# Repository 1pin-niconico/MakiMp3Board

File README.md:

# MakiMp3Board

逐次ファイル等アップロードしていきます。

KiCADは7.0です。

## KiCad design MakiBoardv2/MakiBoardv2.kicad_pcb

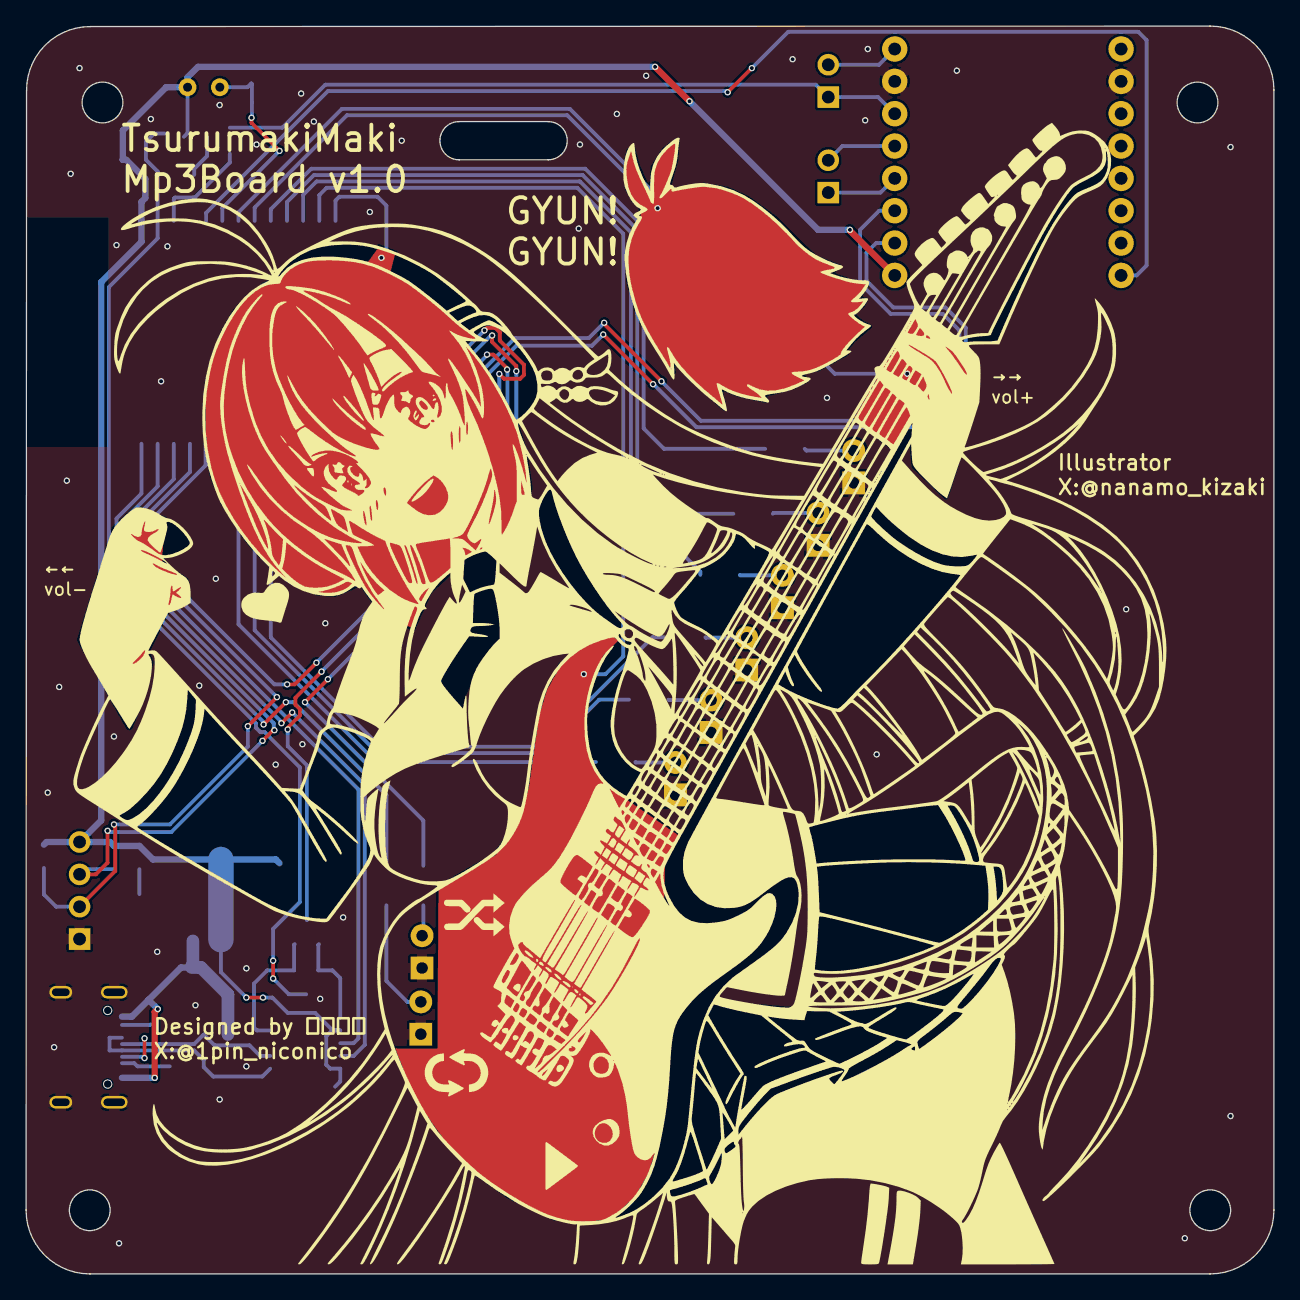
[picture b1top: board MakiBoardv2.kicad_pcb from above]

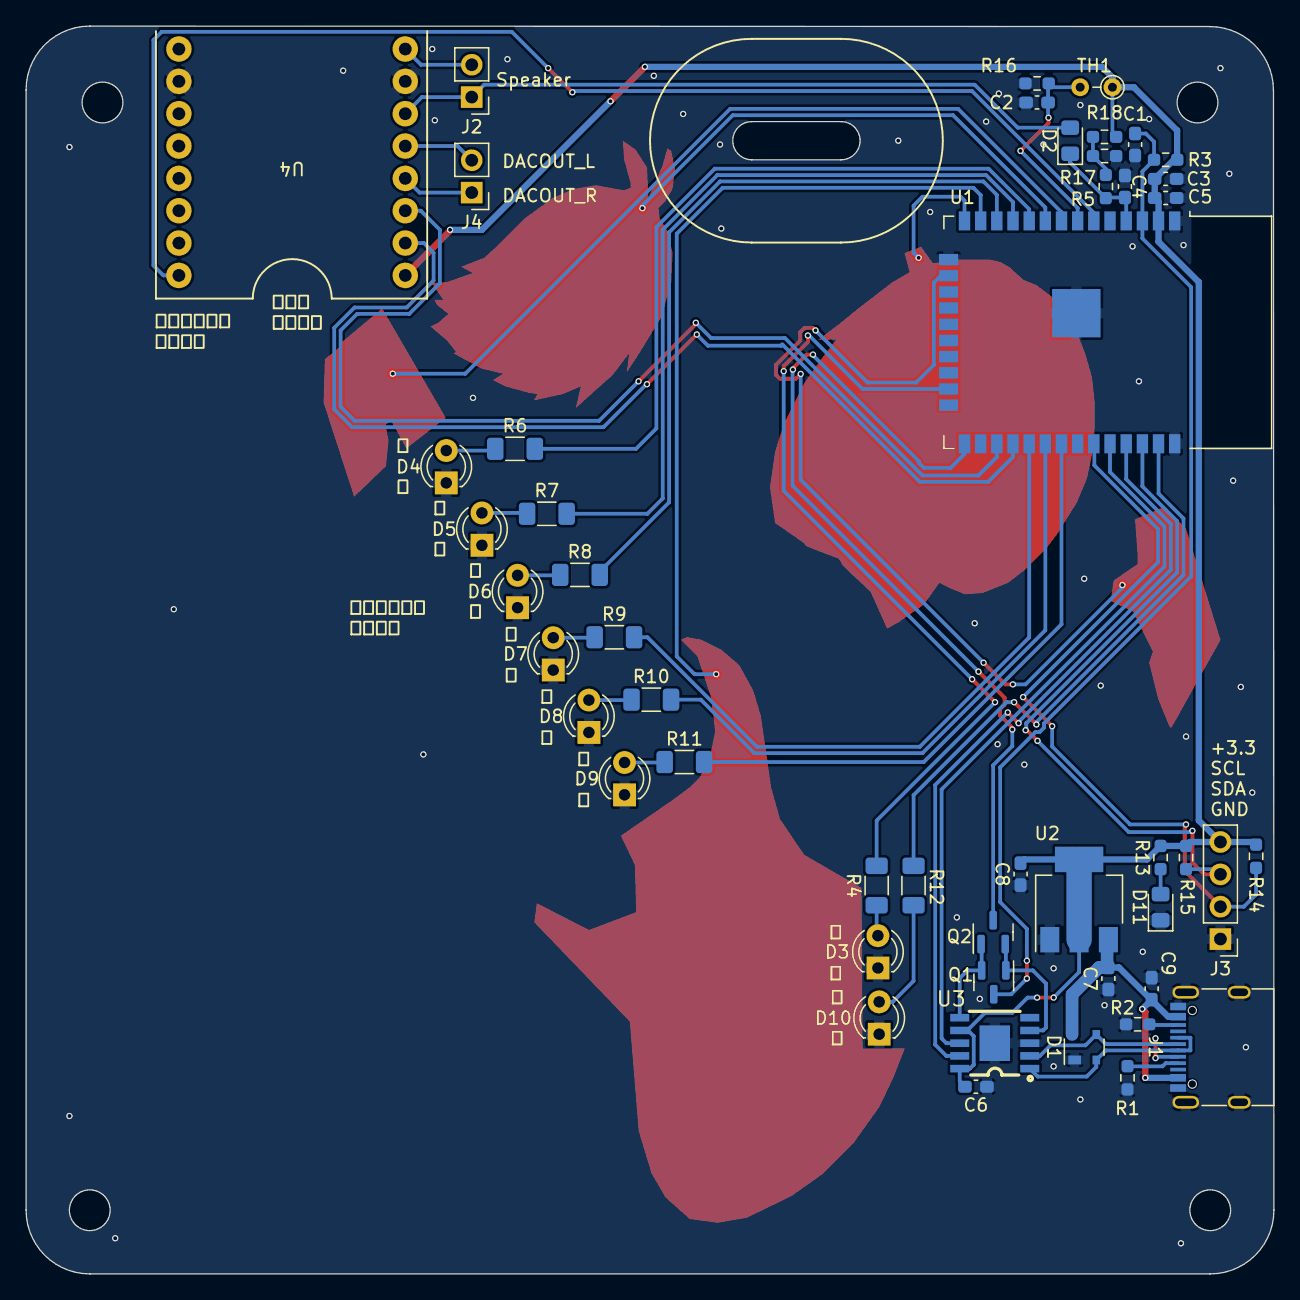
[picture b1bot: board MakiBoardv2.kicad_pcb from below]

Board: 2 copper layers, 98.0 x 98.0 mm, 49 parts (49 on the bottom side), 42 nets.

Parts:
C1, C2, C4, C6: 0.1u; C_0603_1608Metric_Pad1.08x0.95mm_HandSolder
C3, C7, C8, C9: 22u; C_0603_1608Metric_Pad1.08x0.95mm_HandSolder
C5: 1u; C_0603_1608Metric_Pad1.08x0.95mm_HandSolder
D1: PRTR5V0U2X; SOT-143
D2: D_Schottky; D_0805_2012Metric_Pad1.15x1.40mm_HandSolder
D3, D4, D5, D6, D7, D8, D9, D10: LED; LED_D3.0mm
D11: LED; LED_0805_2012Metric_Pad1.15x1.40mm_HandSolder
J1: USB_C_Receptacle_USB2.0; USB_C_Receptacle_G-Switch_GT-USB-7010ASV
J2: speaker; PinHeader_1x02_P2.54mm_Vertical
J3: Conn_01x04_Socket; PinHeader_1x04_P2.54mm_Vertical
J4: Out_speaker; PinHeader_1x02_P2.54mm_Vertical
Q1, Q2: Q_NMOS_GSD; SOT-23
R1, R2: 4.99k; R_0603_1608Metric_Pad0.98x0.95mm_HandSolder
R3, R5, R14, R15, R16: 10k; R_0603_1608Metric_Pad0.98x0.95mm_HandSolder
R4, R6, R7, R8, R9, R10, R11, R12: 220; R_1206_3216Metric_Pad1.30x1.75mm_HandSolder
R13: 220; R_0603_1608Metric_Pad0.98x0.95mm_HandSolder
R17, R18: 1k; R_0603_1608Metric_Pad0.98x0.95mm_HandSolder
TH1: Thermistor; R_Axial_DIN0204_L3.6mm_D1.6mm_P2.54mm_Vertical
U1: ESP32-WROOM-32E; ESP32-WROOM-32D
U2: AZ1117-3.3; SOT-223
U3: CH340K
U4: MP3-TF-16P

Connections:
/3.3V: C3.1, C4.2, C6.2, C8.2, J3.4, R3.2, R13.2, R14.2, R15.2, R18.2, TH1.1, U1.2 (VDD), U2.2 (VO), U2.4 (VO), U3.7 (VCC), U3.10 (V3), U4.1 (VCC)
/BUSY: U1.6 (IO34), U4.16 (BUSY)
/D+: D1.2 (I/O1), J1.A6 (D+), J1.B6 (D+), U3.1 (UD+)
/D-: D1.3 (I/O2), J1.A7 (D-), J1.B7 (D-), U3.2 (UD-)
/EN: C1.1, Q1.3 (D), R3.1, U1.3 (EN)
/ESP_RX0: U1.34 (RXD0/IO3), U3.8 (TXD)
/ESP_RX2: U1.27 (IO16), U4.3 (TX)
/ESP_TX0: U1.35 (TXD0/IO1), U3.9 (RXD)
/ESP_TX2: U1.28 (IO17), U4.2 (RX)
/IO0: Q2.3 (D), U1.25 (IO0)
/LED1: R6.2, U1.10 (IO25)
/LED2: R7.2, U1.11 (IO26)
/LED3: R8.2, U1.12 (IO27)
/LED4: R9.2, U1.29 (IO5)
/LED5: R10.2, U1.30 (IO18)
/LED6: R11.2, U1.31 (IO19)
/LED_MODE: R12.2, U1.37 (IO23)
/LED_SHUFF: R4.2, U1.23 (IO15)
/SCL: J3.3, R15.1, U1.36 (IO22)
/SDA: J3.2, R14.1, U1.33 (IO21)
/SPK1: D2.2 (A), J2.1, U4.6 (SPK_1)
/SPK2: J2.2, U4.8 (SPK_2)
/VT: C2.2, R16.2, TH1.2, U1.7 (IO35)
GND: C1.2, C2.1, C3.2, C4.1, C5.1, C6.1, C7.1, C8.1, C9.2, D1.1 (GND), D3.1 (K), D4.1 (K), D5.1 (K), D6.1 (K), D7.1 (K), D8.1 (K), D9.1 (K), D10.1 (K), D11.1 (K), J1.A1 (GND), J1.A12 (GND), J1.B1 (GND), J1.B12 (GND), J1.S1 (SHIELD), J3.1, R1.1, R2.1, R16.1, R17.2, U1.1 (GND), U1.15 (GND), U1.38 (GND), U1.39 (GND), U2.1 (GND), U3.3 (GND), U3.11 (TP), U4.7 (GND), U4.10 (GND)
unnamed: C7.2, C9.1, D1.4 (VCC), J1.A4 (VBUS), J1.A9 (VBUS), J1.B4 (VBUS), J1.B9 (VBUS), U2.3 (VI)
unnamed: C5.2, D2.1 (K), R5.2, U1.4 (SENSOR_VP)
unnamed: D3.2 (A), R4.1
unnamed: D4.2 (A), R6.1
unnamed: D5.2 (A), R7.1
unnamed: D6.2 (A), R8.1
unnamed: D7.2 (A), R9.1
unnamed: D8.2 (A), R10.1
unnamed: D9.2 (A), R11.1
unnamed: D10.2 (A), R12.1
unnamed: D11.2 (A), R13.1
unnamed: J1.A5 (CC1), R1.2
unnamed: J1.B5 (CC2), R2.2
unnamed: J4.1, U4.4 (DAC_R)
unnamed: J4.2, U4.5 (DAC_L)
unnamed: Q1.1 (G), Q2.2 (S), U3.4 (~DTR)
unnamed: Q1.2 (S), Q2.1 (G), U3.6 (~RTS)
unnamed: R5.1, R17.1, R18.1

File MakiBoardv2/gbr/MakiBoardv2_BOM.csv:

Comment,Designator,Footprint,JLCPCB Part #
0.1u,"C1, C2, C4, C6",Capacitor_SMD:C_0603_1608Metric_Pad1.08x0.95mm_HandSolder,C14663
22u,"C3, C7, C8, C9",Capacitor_SMD:C_0603_1608Metric_Pad1.08x0.95mm_HandSolder,C59461
1u,C5,Capacitor_SMD:C_0603_1608Metric_Pad1.08x0.95mm_HandSolder,C15849
PRTR5V0U2X,D1,Package_TO_SOT_SMD:SOT-143,C3018477
D_Schottky,D2,Diode_SMD:D_0805_2012Metric_Pad1.15x1.40mm_HandSolder,C305421
LED,D11,LED_SMD:LED_0805_2012Metric_Pad1.15x1.40mm_HandSolder,C2297
USB_C_Receptacle_USB2.0,J1,Connector_USB:USB_C_Receptacle_G-Switch_GT-USB-7010ASV,C2988369
Q_NMOS_GSD,"Q1, Q2",Package_TO_SOT_SMD:SOT-23,C8545
4.99k,"R1, R2",Resistor_SMD:R_0603_1608Metric_Pad0.98x0.95mm_HandSolder,C23046
10k,"R3, R5, R14, R15, R16",Resistor_SMD:R_0603_1608Metric_Pad0.98x0.95mm_HandSolder,C25804
220,R13,Resistor_SMD:R_0603_1608Metric_Pad0.98x0.95mm_HandSolder,C22962
1k,"R17, R18",Resistor_SMD:R_0603_1608Metric_Pad0.98x0.95mm_HandSolder,C21190
ESP32-WROOM-32E,U1,RF_Module:ESP32-WROOM-32D,C701341
AZ1117-3.3,U2,Package_TO_SOT_SMD:SOT-223,C108494
CH340K,U3,Makiboard:CH340K,C968586

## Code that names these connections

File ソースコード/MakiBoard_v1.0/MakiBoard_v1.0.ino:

#include "Arduino.h"
#include "EEPROM.h"
#include "BluetoothSerial.h"
#include "WiFi.h"
#include "DFMiniMp3.h"

class Mp3Notify; 
typedef DFMiniMp3<HardwareSerial, Mp3Notify> DfMp3; 
DfMp3 dfmp3(Serial2);

#define LED6 19
#define LED5 18
#define LED4 5
#define LED3 27
#define LED2 26
#define LED1 25
#define LED_LOOP 23
#define LED_SHUFF 15

int playMode=0; //0:mp3再生モード,1:めざましモード
bool tempPause =false; //ポーズ中か否か
bool autoPlay = false; //自動再生モードか否か
bool playFinish = false; //再生が完了しているか否か
bool shuffle = false; //シャッフルモードか否か
bool alert = false;//目覚まし中かどうか
uint32_t timerEN=0;//タイマーモードの可否、上位8bitに目覚ましを鳴らす時刻、下位24bitに時報のEnableが格納
uint8_t previousTrack=0;//最後に再生したトラック
uint8_t f1Number;//フォルダ1内のトラック数
uint8_t f3Number;
uint8_t randomArray[256];

String SSID;//WiFi接続時のSSID格納変数
String PASS;//WiFi接続時のパスワード格納変数
//DFRobotDFPlayerMini myDFPlayer;
BluetoothSerial SerialBT;//Bluetooth
struct tm timeInfo;

int vol=20;//ボリューム0~30

int TC4,TC5,TC6,TC8,TC9;//タッチセンサの初期値
int TCth=10;//タッチセンサの反応閾値
uint32_t TC4time=0;//タッチセンサのタッチ時間
uint32_t TC5time=0;
uint32_t TC6time=0;
uint32_t TC8time=0;
uint32_t TC9time=0;

uint32_t stopTime = 0; //再生を終えた時刻
uint32_t previousCheckTime=0; //時刻監視を最後にした時刻
uint8_t previousHour; //今何時？
uint32_t volLEDsetTime=0;//ボリュームを最後に設定した時刻

uint32_t LEDbias=1800;
uint32_t LEDth=50;

class Mp3Notify
{
public:
  static void PrintlnSourceAction(DfMp3_PlaySources source, const char* action)
  {
    if (source & DfMp3_PlaySources_Sd) 
    {
        Serial.print("SD Card, ");
    }
    if (source & DfMp3_PlaySources_Usb) 
    {
        Serial.print("USB Disk, ");
    }
    if (source & DfMp3_PlaySources_Flash) 
    {
        Serial.print("Flash, ");
    }
    Serial.println(action);
  }
  static void OnError([[maybe_unused]] DfMp3& mp3, uint16_t errorCode)
  {
    // see DfMp3_Error for code meaning
    Serial.println();
    Serial.print("Com Error ");
    Serial.println(errorCode);
  }
  static void OnPlayFinished([[maybe_unused]] DfMp3& mp3, [[maybe_unused]] DfMp3_PlaySources source, uint16_t track)
  {
    Serial.print("Play finished for #");
    Serial.println(track);  
  }
  static void OnPlaySourceOnline([[maybe_unused]] DfMp3& mp3, DfMp3_PlaySources source)
  {
    PrintlnSourceAction(source, "online");
  }
  static void OnPlaySourceInserted([[maybe_unused]] DfMp3& mp3, DfMp3_PlaySources source)
  {
    PrintlnSourceAction(source, "inserted");
  }
  static void OnPlaySourceRemoved([[maybe_unused]] DfMp3& mp3, DfMp3_PlaySources source)
  {
    PrintlnSourceAction(source, "removed");
  }
};

void setup() {
    Serial.begin(115200);//PCとの通信用
    //Serial2.begin(9600);//MP3playerとの通信用
    SerialBT.begin("MakiMp3Player");//Bluetoth用

    pinSetup();
    readEEPROM();
    MP3Setup();
   
    if(SSID.length()>0&&PASS.length()>0){
        connectWiFi();
        timeFix();
        previousHour=timeInfo.tm_hour;
    }
    setTC();

    //Serial.print("フォルダ内mp3数:");
    //Serial.println(f3Number);
    createArray();
}

void loop() {

    touchFunction();

    uint32_t ADC=analogRead(36);
    if(millis()-volLEDsetTime>3000)volumeLED(ADC);

    uint32_t temp=analogRead(35);
    if(playMode==1&&temp>100&&CTemp(temp)>40.0&&playFinish&&previousCheckTime-stopTime>600000){
        dfmp3.playFolderTrack(2,26);
        playFinish=false;
        stopTime=millis();
    }

    if(Serial.available()){
        delay(10);
        String data = Serial.readStringUntil(';');
        serialDecode(data);
    }

    if(millis()-previousCheckTime>1000){
        if(temp>100){
            SerialBT.print(CTemp(temp),1);
            SerialBT.println(" ℃");
        }
        previousCheckTime=millis();
        if(playMode==1){
            Alert();
        }
    }

    if(digitalRead(34)==HIGH)playFinish=true;
    else playFinish=false;
    
    if(autoPlay&&playFinish&&!tempPause)playNext();
    if(playFinish&&alert)playAlertMusic();
    delay(10);
}

void pinSetup(){
    pinMode(36,ANALOG);
    pinMode(35,ANALOG);
    pinMode(LED1,OUTPUT);
    pinMode(LED2,OUTPUT);
    pinMode(LED3,OUTPUT);
    pinMode(LED4,OUTPUT);
    pinMode(LED5,OUTPUT);
    pinMode(LED6,OUTPUT);
    pinMode(34,INPUT);
    pinMode(LED_LOOP,OUTPUT);
    pinMode(LED_SHUFF,OUTPUT);
}

float CTemp(uint32_t vt){
    return(vt-850-160)/32.0;
}

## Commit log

2023-09-29 Create KiCAD
2023-09-29 Add files via upload
    マキ基板の設計図です。KiCAD7.0なので注意！
